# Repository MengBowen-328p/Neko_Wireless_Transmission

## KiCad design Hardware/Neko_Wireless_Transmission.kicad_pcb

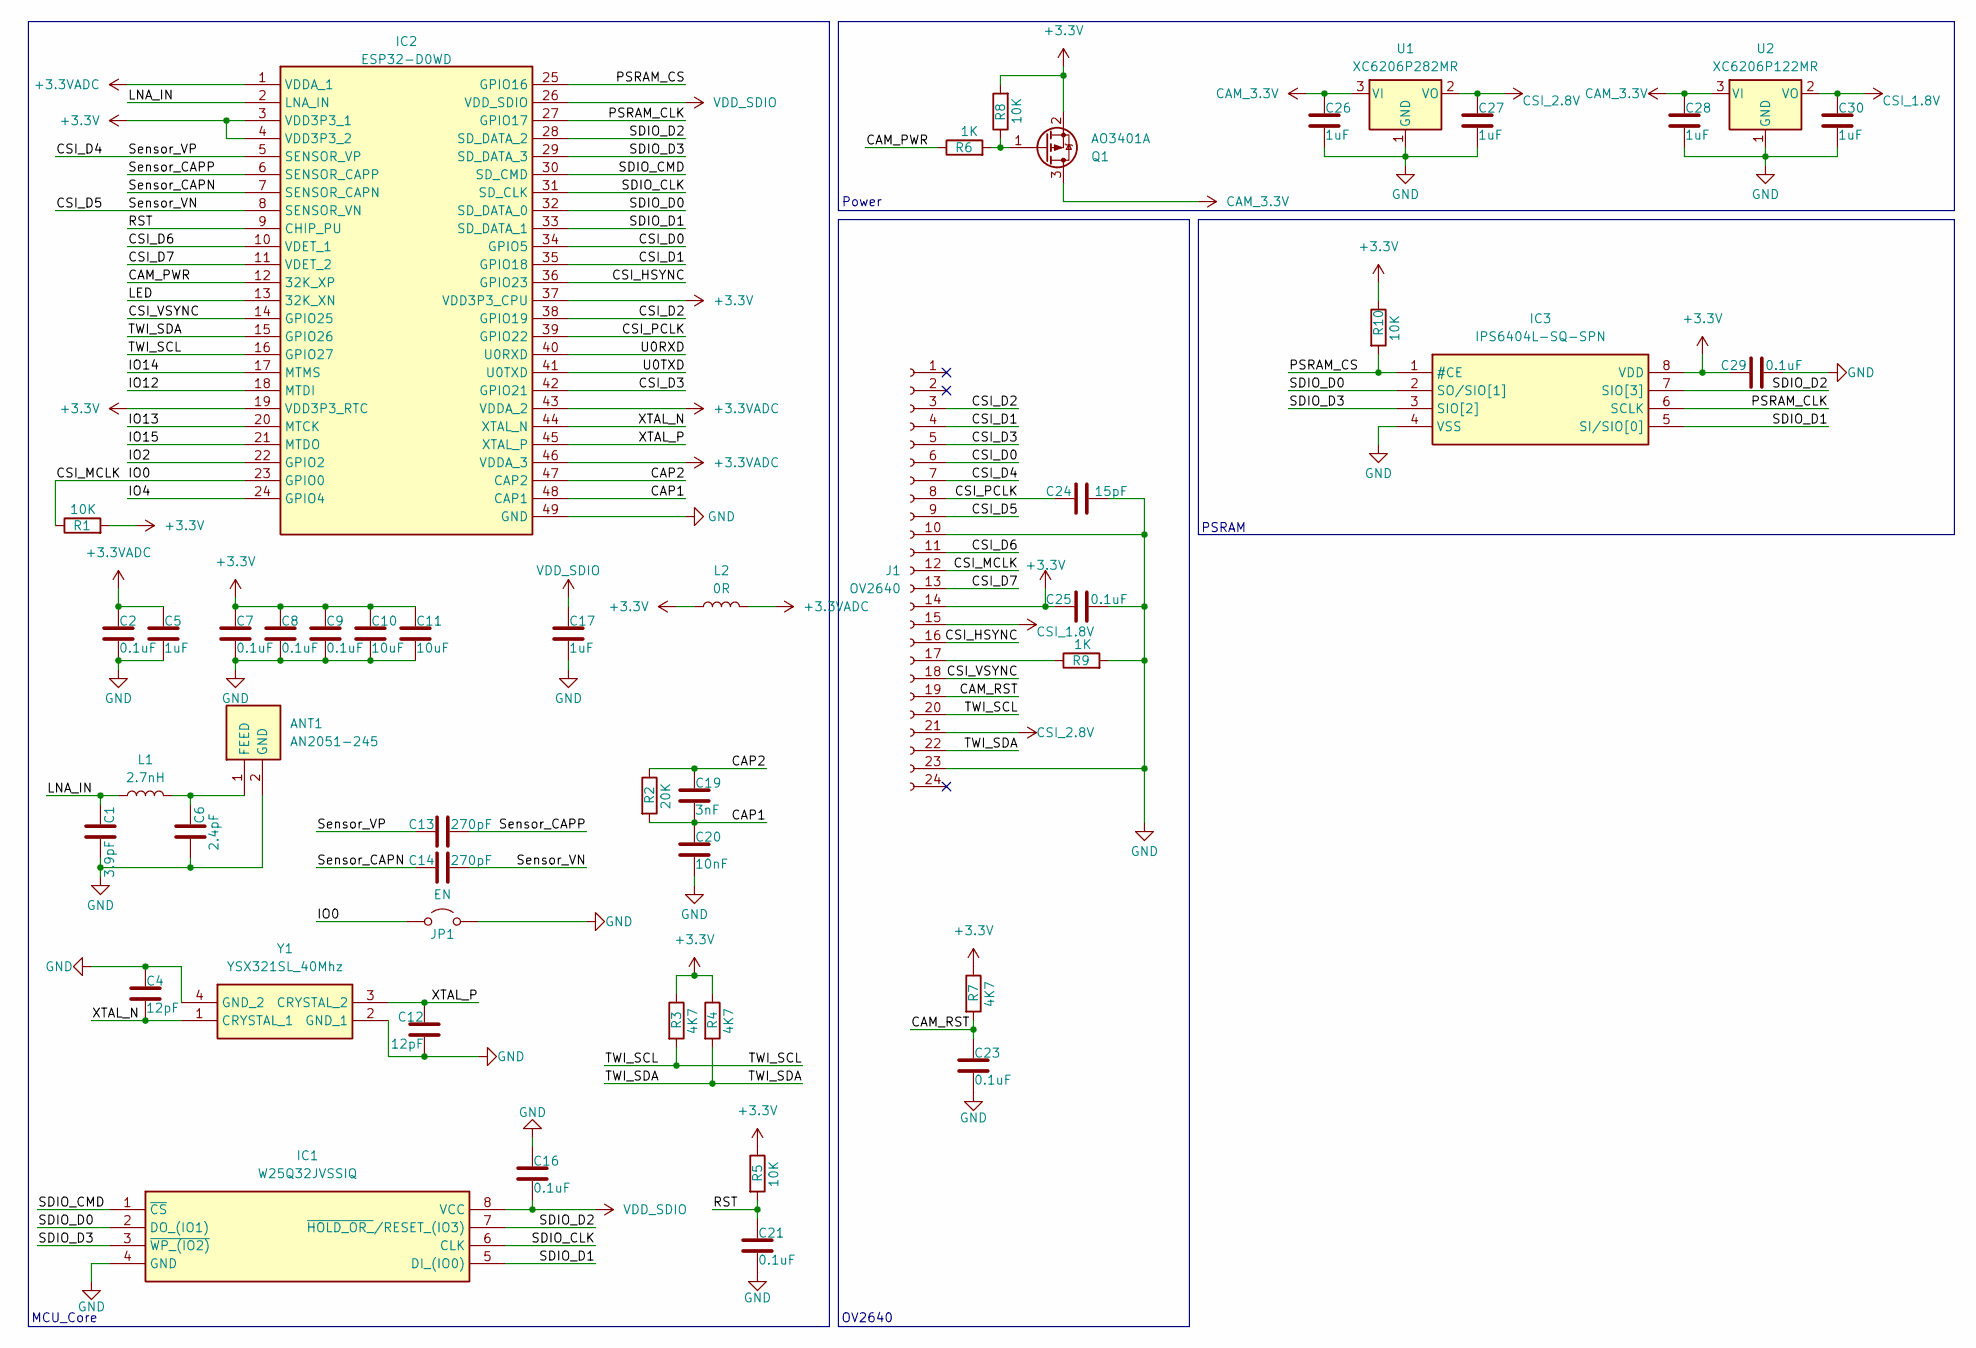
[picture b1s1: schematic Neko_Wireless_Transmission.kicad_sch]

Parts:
ANT1: AN2051-245; ANTC5020X127N; Manufacturer_Part_Number AN2051-245
C1: 3.9pF; C_0402_1005Metric
C2, C7, C8, C9, C16, C21, C23, C25, C29: 0.1uF; C_0402_1005Metric
C4, C12: 12pF; C_0402_1005Metric
C5, C17: 1uF; C_0402_1005Metric
C6: 2.4pF; C_0402_1005Metric
C10, C11: 10uF; C_0402_1005Metric
C13, C14: 270pF; C_0402_1005Metric
C19: 3nF; C_0402_1005Metric
C20: 10nF; C_0402_1005Metric
C24: 15pF; C_0402_1005Metric
C26, C27, C28, C30: 1uF; C_0603_1608Metric
IC1: W25Q32JVSSIQ; SOIC127P790X216-8N; Manufacturer_Part_Number W25Q32JVSSIQ; Mouser Part Number 454-W25Q32JVSSIQ
IC2: ESP32-D0WD; QFN40P600X600X90-49N-D; Manufacturer_Part_Number ESP32-D0WD; Mouser Part Number 356-ESP32-D0WD
IC3: IPS6404L-SQ-SPN; SOIC127P600X175-8N; Manufacturer_Part_Number IPS6404L-SQ-SPN
J1: OV2640; TE_2-1734839-4_1x24-1MP_P0.5mm_Horizontal
JP1: EN; SolderJumper-2_P1.3mm_Open_RoundedPad1.0x1.5mm
L1: 2.7nH; L_0402_1005Metric_Pad0.77x0.64mm_HandSolder
L2: 0R; L_0402_1005Metric_Pad0.77x0.64mm_HandSolder
Q1: AO3401A; SOT-23
R1, R5, R8, R10: 10K; R_0402_1005Metric
R2: 20K; R_0402_1005Metric
R3, R4, R7: 4K7; R_0402_1005Metric
R6, R9: 1K; R_0402_1005Metric
U1: XC6206P282MR; SOT-23-3
U2: XC6206P122MR; SOT-23-3
Y1: YSX321SL_40Mhz; YSX321SL; Manufacturer_Part_Number YSX321SL

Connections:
+3.3V: C7.1, C8.1, C9.1, C10.1, C11.1, C25.1, C29.1, IC2.3 (VDD3P3_1), IC2.4 (VDD3P3_2), IC2.19 (VDD3P3_RTC), IC2.37 (VDD3P3_CPU), IC3.8 (VDD), J1.14, L2.1, Q1.2 (S), R1.2, R3.1, R4.1, R5.1, R7.1, R8.2, R10.1
+3.3VADC: C2.1, C5.1, IC2.1 (VDDA_1), IC2.43 (VDDA_2), IC2.46 (VDDA_3), L2.2
/CAM_PWR: IC2.12 (32K_XP), R6.1
/CAM_RST: C23.1, J1.19, R7.2
/CAP1: C19.2, C20.1, IC2.48 (CAP1), R2.2
/CAP2: C19.1, IC2.47 (CAP2), R2.1
/CSI_D0: IC2.34 (GPIO5), J1.6
/CSI_D1: IC2.35 (GPIO18), J1.4
/CSI_D2: IC2.38 (GPIO19), J1.3
/CSI_D3: IC2.42 (GPIO21), J1.5
/CSI_D4: C13.1, IC2.5 (SENSOR_VP), J1.7
/CSI_D5: C14.2, IC2.8 (SENSOR_VN), J1.9
/CSI_D6: IC2.10 (VDET_1), J1.11
/CSI_D7: IC2.11 (VDET_2), J1.13
/CSI_HSYNC: IC2.36 (GPIO23), J1.16
/CSI_MCLK: IC2.23 (GPIO0), J1.12, JP1.1 (A), R1.1
/CSI_PCLK: C24.1, IC2.39 (GPIO22), J1.8
/CSI_VSYNC: IC2.14 (GPIO25), J1.18
/IO2: IC2.22 (GPIO2)
/IO4: IC2.24 (GPIO4)
/IO12: IC2.18 (MTDI)
/IO13: IC2.20 (MTCK)
/IO14: IC2.17 (MTMS)
/IO15: IC2.21 (MTDO)
/LED: IC2.13 (32K_XN)
/LNA_IN: C1.1, IC2.2 (LNA_IN), L1.1
/PSRAM_CLK: IC2.27 (GPIO17), IC3.6 (SCLK)
/PSRAM_CS: IC2.25 (GPIO16), IC3.1 (#CE), R10.2
/RST: C21.1, IC2.9 (CHIP_PU), R5.2
/SDIO_CLK: IC1.6 (CLK), IC2.31 (SD_CLK)
/SDIO_CMD: IC1.1 (~CS), IC2.30 (SD_CMD)
/SDIO_D0: IC1.2 (DO_(IO1)), IC2.32 (SD_DATA_0), IC3.2 (SO/SIO[1])
/SDIO_D1: IC1.5 (DI_(IO0)), IC2.33 (SD_DATA_1), IC3.5 (SI/SIO[0])
/SDIO_D2: IC1.7 (~HOLD_OR_/RESET_(IO3)), IC2.28 (SD_DATA_2), IC3.7 (SIO[3])
/SDIO_D3: IC1.3 (~WP_(IO2)), IC2.29 (SD_DATA_3), IC3.3 (SIO[2])
/Sensor_CAPN: C14.1, IC2.7 (SENSOR_CAPN)
/Sensor_CAPP: C13.2, IC2.6 (SENSOR_CAPP)
/TWI_SCL: IC2.16 (GPIO27), J1.20, R3.2
/TWI_SDA: IC2.15 (GPIO26), J1.22, R4.2
/U0RXD: IC2.40 (U0RXD)
/U0TXD: IC2.41 (U0TXD)
/XTAL_N: C4.2, IC2.44 (XTAL_N), Y1.1 (CRYSTAL_1)
/XTAL_P: C12.1, IC2.45 (XTAL_P), Y1.3 (CRYSTAL_2)
CAM_3.3V: C26.1, C28.1, Q1.3 (D), U1.3 (VI), U2.3 (VI)
CSI_1.8V: C30.1, J1.15, U2.2 (VO)
CSI_2.8V: C27.1, J1.21, U1.2 (VO)
GND: ANT1.2 (GND), C1.2, C2.2, C4.1, C5.2, C6.2, C7.2, C8.2, C9.2, C10.2, C11.2, C12.2, C16.1, C17.2, C20.2, C21.2, C23.2, C24.2, C25.2, C26.2, C27.2, C28.2, C29.2, C30.2, IC1.4 (GND), IC2.49 (GND), IC3.4 (VSS), J1.10, J1.23, JP1.2 (B), R9.2, U1.1 (GND), U2.1 (GND), Y1.2 (GND_1), Y1.4 (GND_2)
unnamed: ANT1.1 (FEED), C6.1, L1.2
unnamed: J1.17, R9.1
unnamed: Q1.1 (G), R6.2, R8.1
VDD_SDIO: C16.2, C17.1, IC1.8 (VCC), IC2.26 (VDD_SDIO)

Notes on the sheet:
Power
PSRAM
OV2640
MCU_Core

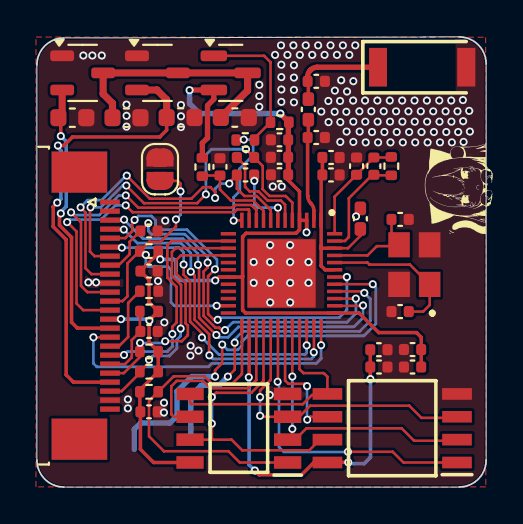
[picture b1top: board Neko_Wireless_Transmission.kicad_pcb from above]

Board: 2 copper layers, 25.0 x 25.0 mm, 48 parts (0 on the bottom side), 42 nets.

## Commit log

2024-10-09 Update New PCB Layput
2024-10-09 Finished PCB Layout
